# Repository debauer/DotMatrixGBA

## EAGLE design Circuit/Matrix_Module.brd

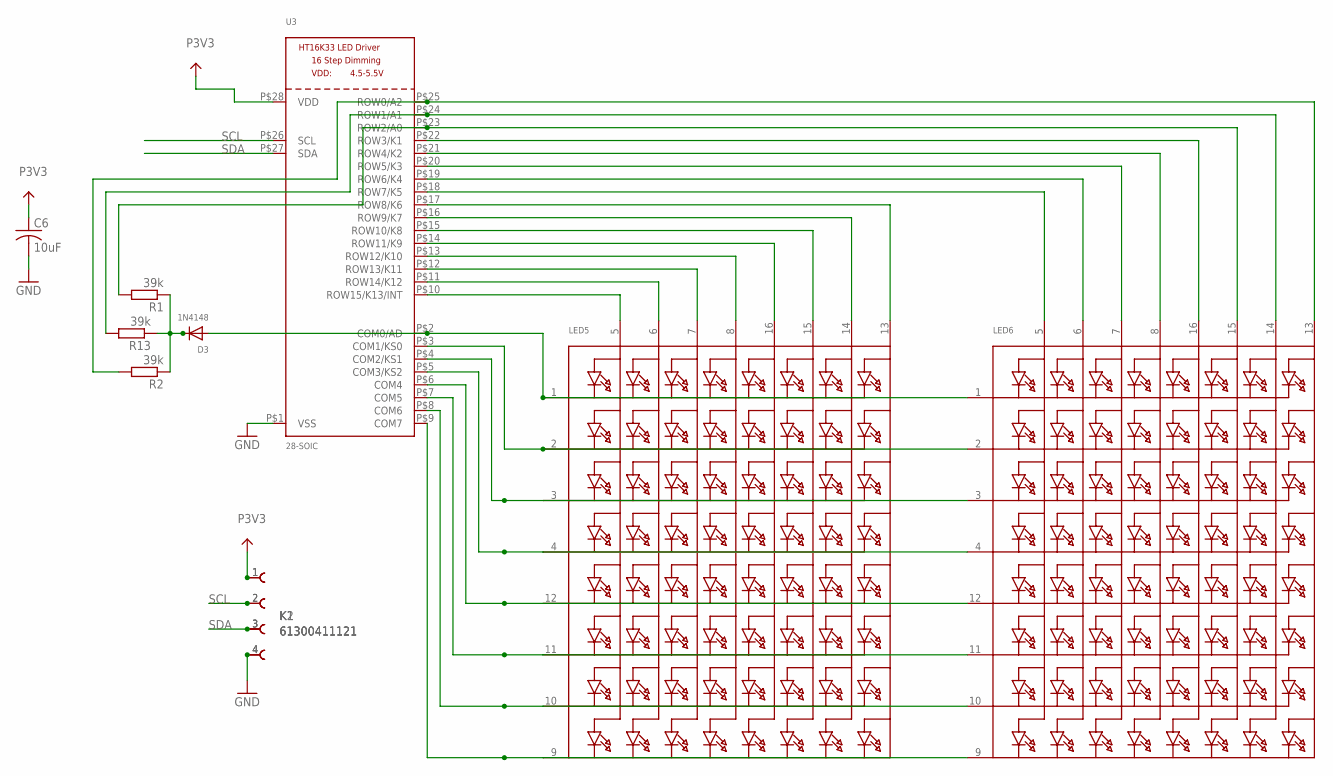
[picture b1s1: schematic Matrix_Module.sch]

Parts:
C6: 10uF; C0805
D3: 1N4148; SOD-323F
K1, K2: 61300411121
LED5, LED6: SEGMENT_8X8_ROWCATHODE; SEGMENT_BL-M07C881UR
R1, R2, R13: 39k; R0805
U3: 28-SOIC; SOP28_300MIL

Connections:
GND: C6.2, K1.4, K2.4, U3.P$1 (VSS)
unnamed: LED6.13 (A8), R2.2, U3.P$25 (ROW0/A2)
unnamed: LED6.14 (A7), R13.2, U3.P$24 (ROW1/A1)
unnamed: LED6.15 (A6), R1.2, U3.P$23 (ROW2/A0)
unnamed: LED5.9 (K8), LED6.9 (K8), U3.P$9 (COM7)
unnamed: LED5.10 (K7), LED6.10 (K7), U3.P$8 (COM6)
unnamed: LED5.11 (K6), LED6.11 (K6), U3.P$7 (COM5)
unnamed: LED5.12 (K5), LED6.12 (K5), U3.P$6 (COM4)
unnamed: LED5.4 (K4), LED6.4 (K4), U3.P$5 (COM3/KS2)
unnamed: LED5.3 (K3), LED6.3 (K3), U3.P$4 (COM2/KS1)
unnamed: LED5.6 (A2), U3.P$11 (ROW14/K12)
unnamed: LED5.7 (A3), U3.P$12 (ROW13/K11)
unnamed: LED6.5 (A1), U3.P$18 (ROW7/K5)
unnamed: LED6.8 (A4), U3.P$21 (ROW4/K2)
unnamed: LED6.7 (A3), U3.P$20 (ROW5/K3)
unnamed: LED5.13 (A8), U3.P$17 (ROW8/K6)
unnamed: LED5.14 (A7), U3.P$16 (ROW9/K7)
unnamed: LED5.16 (A5), U3.P$14 (ROW11/K9)
unnamed: LED5.15 (A6), U3.P$15 (ROW10/K8)
unnamed: LED5.8 (A4), U3.P$13 (ROW12/K10)
unnamed: LED5.5 (A1), U3.P$10 (ROW15/K13/INT)
unnamed: D3.C, R1.1, R2.1, R13.1
unnamed: LED6.16 (A5), U3.P$22 (ROW3/K1)
unnamed: LED6.6 (A2), U3.P$19 (ROW6/K4)
unnamed: D3.A, LED5.1 (K1), LED6.1 (K1), U3.P$2 (COM0/AD)
unnamed: LED5.2 (K2), LED6.2 (K2), U3.P$3 (COM1/KS0)
P3V3: C6.1, K1.1, K2.1, U3.P$28 (VDD)
SCL: K1.2, K2.2, U3.P$26 (SCL)
SDA: K1.3, K2.3, U3.P$27 (SDA)

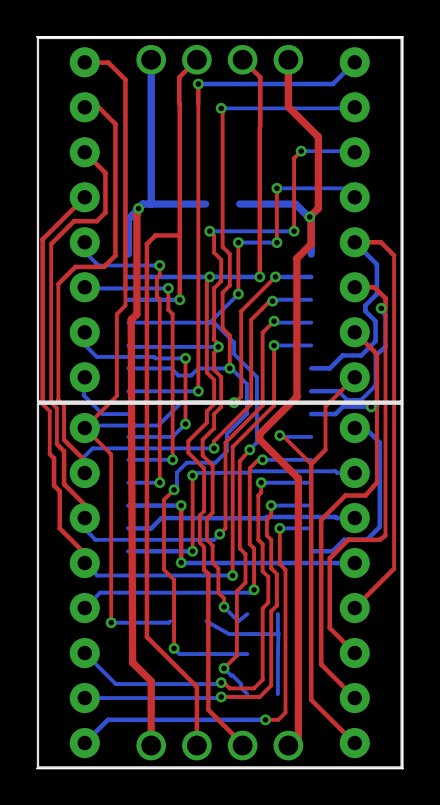
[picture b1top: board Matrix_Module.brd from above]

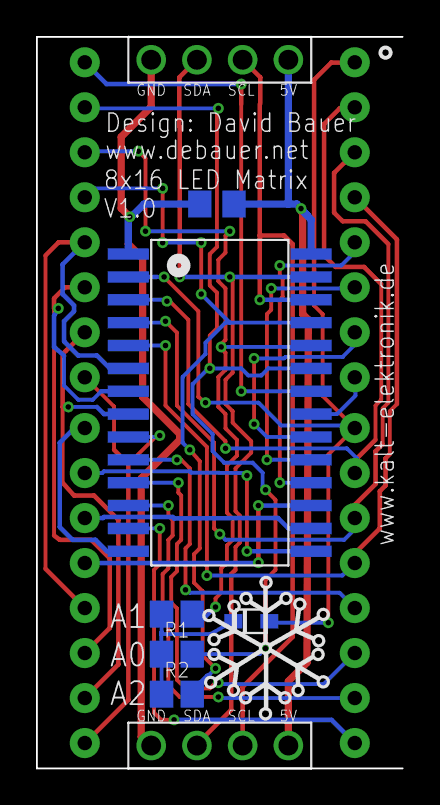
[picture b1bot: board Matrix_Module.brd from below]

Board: 2 copper layers, 20.3 x 40.6 mm, 11 parts (9 on the bottom side), 29 nets.

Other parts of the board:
U$1: SNOW

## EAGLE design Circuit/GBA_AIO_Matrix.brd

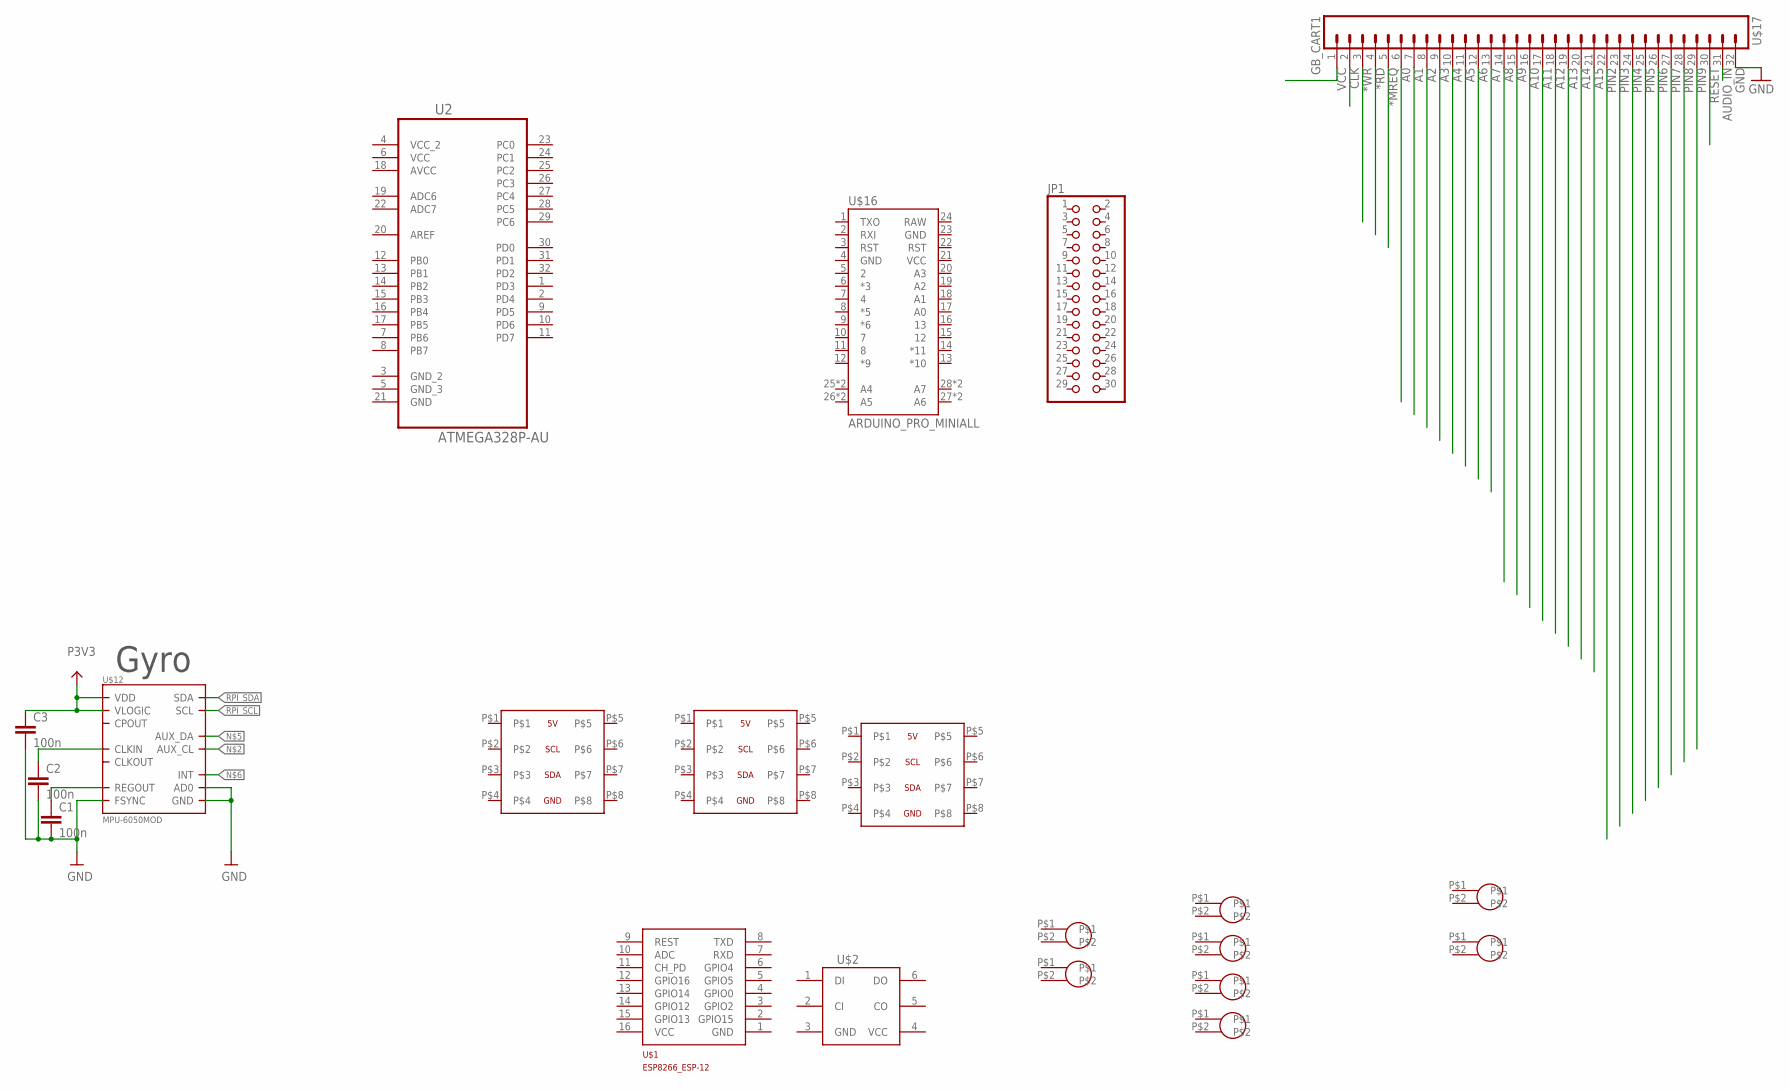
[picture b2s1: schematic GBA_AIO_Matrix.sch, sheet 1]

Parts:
C1, C2, C3: 100n; C0603
JP1: PINHD-2X15/90; 2X15/90
U2: ATMEGA328P-AU; QFP80P900X900X120-32N
U$1: ESP8266_ESP-12; ESP8266-ESP12
U$2: APA102; LED5050
U$4, U$5: GBA_BUTTONAB; GBA_AB
U$6, U$7, U$8, U$9: GBA_BUTTONDIREKTION; GBA_DIREKTION
U$10, U$11: GBA_BUTTONSTART; GBA_START
U$12: MPU-6050MOD; QFN.24.4X4.MOD
U$16: ARDUINO_PRO_MINIALL; ARDUINO_PRO_MINI
U$17: GB_CART1; GB_CART_1
U$18, U$19, U$20: DEBAUER_18X6MATRIX; DEBAUER_16X8MATRIX

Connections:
*MREQ: U$17.5
*RD: U$17.4
*WR: U$17.3
A0: U$17.6; also elsewhere on the board
A1: U$17.7; also elsewhere on the board
A2: U$17.8; also elsewhere on the board
A3: U$17.9
A4: U$17.10
A5: U$17.11
A6: U$17.12
A7: U$17.13
A8: U$17.14
A9: U$17.15
A10: U$17.16
A11: U$17.17
A12: U$17.18
A13: U$17.19
A14: U$17.20
A15: U$17.21
AUDIO_IN: U$17.31
AVCC: U2.18 (AVCC)
GND: C1.2, C2.2, C3.2, U$12.9 (AD0), U$12.11 (FSYNC), U$12.18 (GND), U$17.2, U$17.32; also elsewhere on the board
unnamed: C2.1, U$12.1 (CLKIN)
unnamed: C1.1, U$12.10 (REGOUT)
P3V3: C3.1, U$12.8 (VLOGIC), U$12.13 (VDD); also elsewhere on the board
PIN2: U$17.22
PIN3: U$17.23
PIN4: U$17.24
PIN5: U$17.25
PIN6: U$17.26
PIN7: U$17.27
PIN8: U$17.28
PIN9: U$17.29
RPI_SCL: U$12.23 (SCL)
RPI_SDA: U$12.24 (SDA)
VCC: U2.6 (VCC)
VCC1: U$17.1, U$17.30
VCC_2: U2.4 (VCC_2)

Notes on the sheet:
Gyro
CLK
VCC
RESET

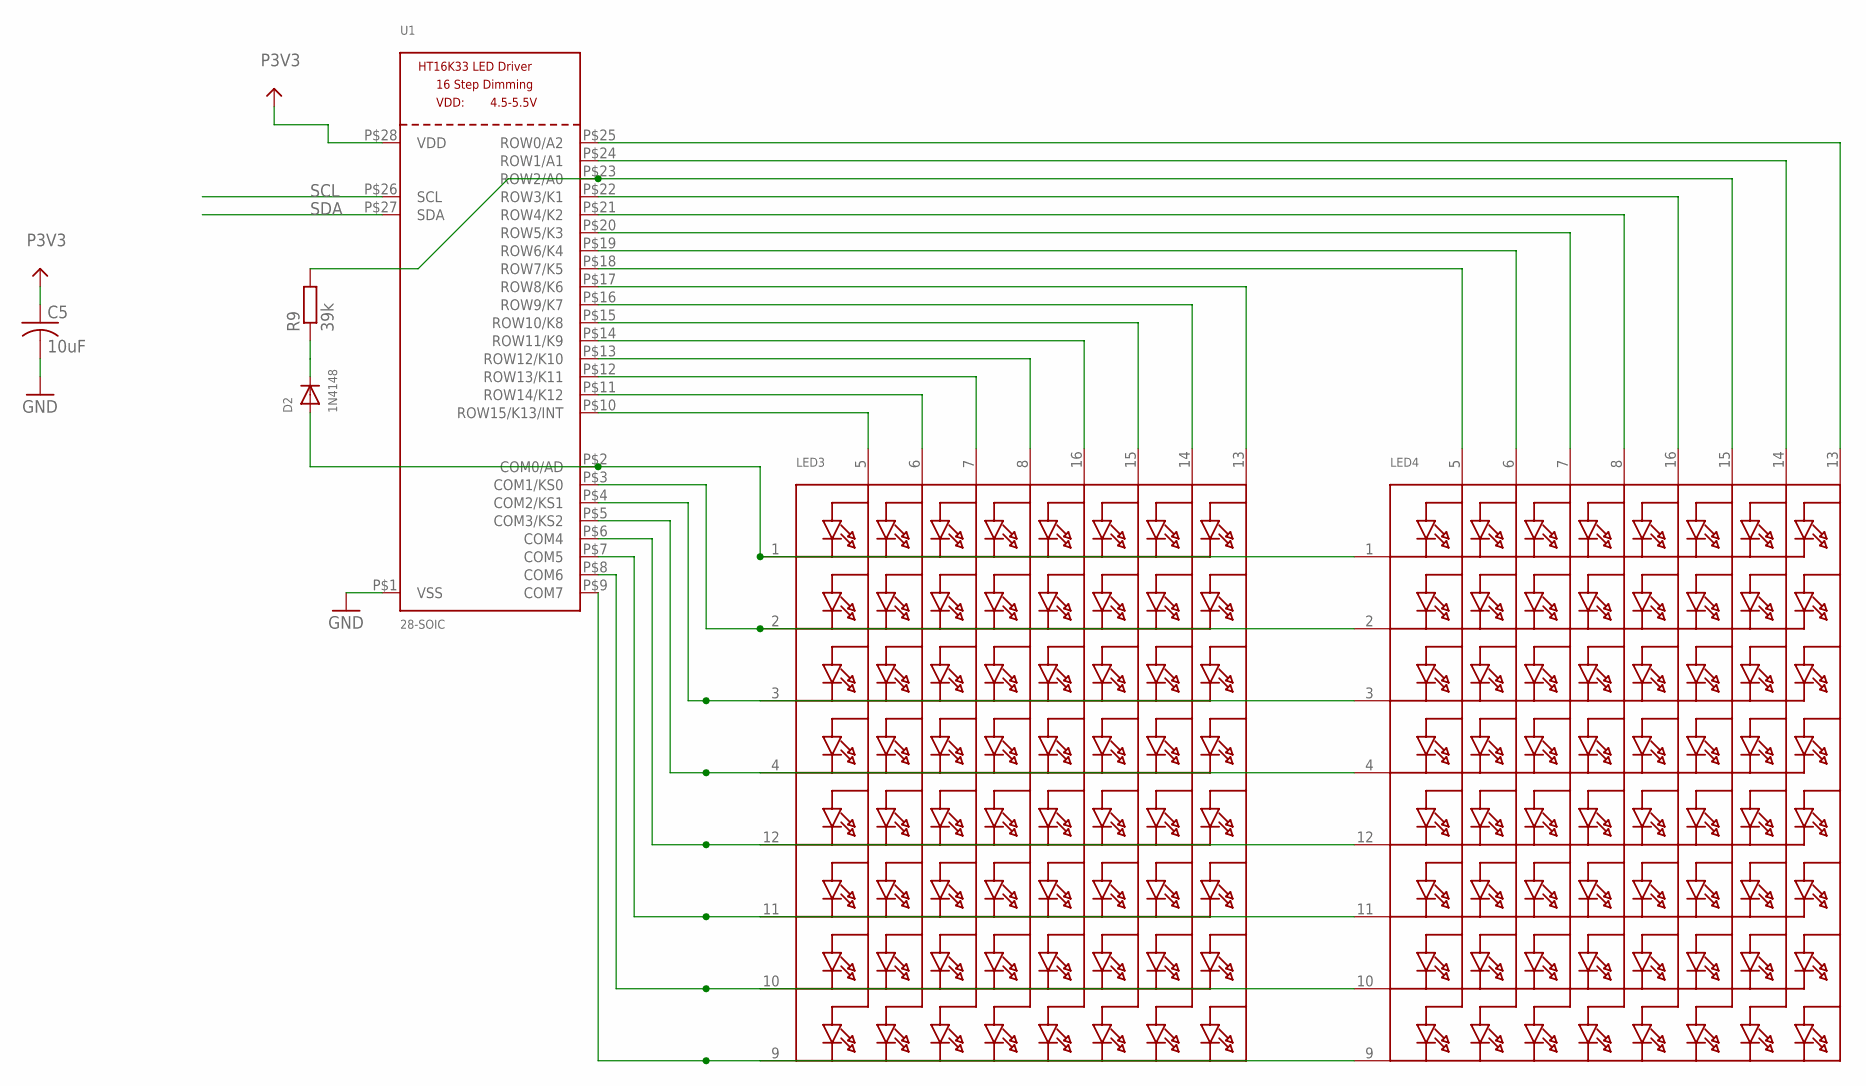
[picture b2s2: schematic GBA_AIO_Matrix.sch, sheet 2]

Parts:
C5: 10uF; C0805
D2: 1N4148; SOD-323F
LED3, LED4: SEGMENT_8X8_ROWCATHODE; SEGMENT_BL-M07C881UR
R9: 39k; R0805
U1: 28-SOIC; SOP28_300MIL

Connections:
GND: C5.2, U1.P$1 (VSS); also elsewhere on the board
unnamed: LED4.13 (A8), U1.P$25 (ROW0/A2)
unnamed: LED4.15 (A6), R9.2, U1.P$23 (ROW2/A0)
unnamed: LED4.14 (A7), U1.P$24 (ROW1/A1)
unnamed: LED3.9 (K8), LED4.9 (K8), U1.P$9 (COM7)
unnamed: LED3.10 (K7), LED4.10 (K7), U1.P$8 (COM6)
unnamed: LED3.11 (K6), LED4.11 (K6), U1.P$7 (COM5)
unnamed: LED3.12 (K5), LED4.12 (K5), U1.P$6 (COM4)
unnamed: LED3.4 (K4), LED4.4 (K4), U1.P$5 (COM3/KS2)
unnamed: LED3.3 (K3), LED4.3 (K3), U1.P$4 (COM2/KS1)
unnamed: LED3.6 (A2), U1.P$11 (ROW14/K12)
unnamed: LED3.7 (A3), U1.P$12 (ROW13/K11)
unnamed: LED4.5 (A1), U1.P$18 (ROW7/K5)
unnamed: LED4.8 (A4), U1.P$21 (ROW4/K2)
unnamed: LED4.7 (A3), U1.P$20 (ROW5/K3)
unnamed: LED3.13 (A8), U1.P$17 (ROW8/K6)
unnamed: LED3.14 (A7), U1.P$16 (ROW9/K7)
unnamed: LED3.16 (A5), U1.P$14 (ROW11/K9)
unnamed: LED3.15 (A6), U1.P$15 (ROW10/K8)
unnamed: LED3.8 (A4), U1.P$13 (ROW12/K10)
unnamed: LED3.5 (A1), U1.P$10 (ROW15/K13/INT)
unnamed: D2.C, R9.1
unnamed: LED4.16 (A5), U1.P$22 (ROW3/K1)
unnamed: LED4.6 (A2), U1.P$19 (ROW6/K4)
unnamed: D2.A, LED3.1 (K1), LED4.1 (K1), U1.P$2 (COM0/AD)
unnamed: LED3.2 (K2), LED4.2 (K2), U1.P$3 (COM1/KS0)
P3V3: C5.1, U1.P$28 (VDD); also elsewhere on the board
SCL: U1.P$26 (SCL); also elsewhere on the board
SDA: U1.P$27 (SDA); also elsewhere on the board

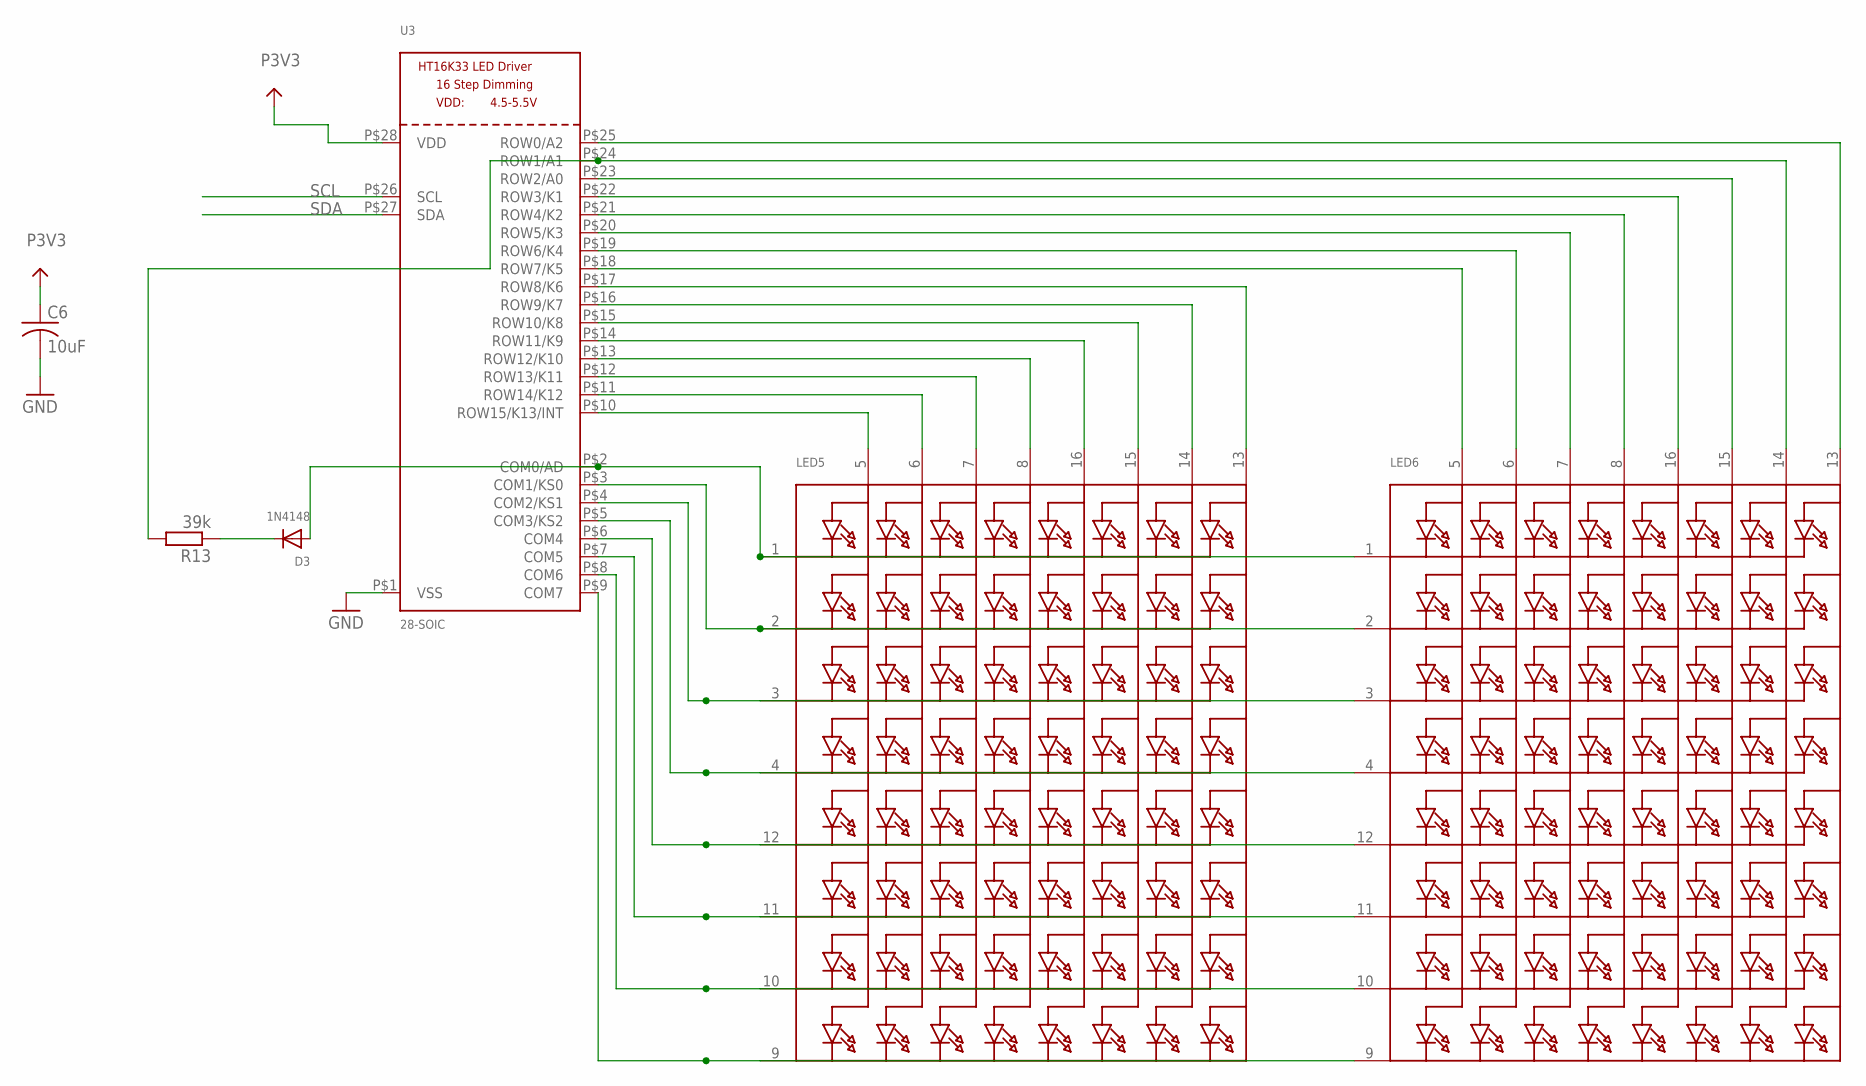
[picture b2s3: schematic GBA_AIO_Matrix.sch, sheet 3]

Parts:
C6: 10uF; C0805
D3: 1N4148; SOD-323F
LED5, LED6: SEGMENT_8X8_ROWCATHODE; SEGMENT_BL-M07C881UR
R13: 39k; R0805
U3: 28-SOIC; SOP28_300MIL

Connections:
GND: C6.2, U3.P$1 (VSS); also elsewhere on the board
unnamed: LED6.13 (A8), U3.P$25 (ROW0/A2)
unnamed: LED6.14 (A7), R13.2, U3.P$24 (ROW1/A1)
unnamed: LED6.15 (A6), U3.P$23 (ROW2/A0)
unnamed: LED5.9 (K8), LED6.9 (K8), U3.P$9 (COM7)
unnamed: LED5.10 (K7), LED6.10 (K7), U3.P$8 (COM6)
unnamed: LED5.11 (K6), LED6.11 (K6), U3.P$7 (COM5)
unnamed: LED5.12 (K5), LED6.12 (K5), U3.P$6 (COM4)
unnamed: LED5.4 (K4), LED6.4 (K4), U3.P$5 (COM3/KS2)
unnamed: LED5.3 (K3), LED6.3 (K3), U3.P$4 (COM2/KS1)
unnamed: LED5.6 (A2), U3.P$11 (ROW14/K12)
unnamed: LED5.7 (A3), U3.P$12 (ROW13/K11)
unnamed: LED6.5 (A1), U3.P$18 (ROW7/K5)
unnamed: LED6.8 (A4), U3.P$21 (ROW4/K2)
unnamed: LED6.7 (A3), U3.P$20 (ROW5/K3)
unnamed: LED5.13 (A8), U3.P$17 (ROW8/K6)
unnamed: LED5.14 (A7), U3.P$16 (ROW9/K7)
unnamed: LED5.16 (A5), U3.P$14 (ROW11/K9)
unnamed: LED5.15 (A6), U3.P$15 (ROW10/K8)
unnamed: LED5.8 (A4), U3.P$13 (ROW12/K10)
unnamed: LED5.5 (A1), U3.P$10 (ROW15/K13/INT)
unnamed: D3.C, R13.1
unnamed: LED6.16 (A5), U3.P$22 (ROW3/K1)
unnamed: LED6.6 (A2), U3.P$19 (ROW6/K4)
unnamed: D3.A, LED5.1 (K1), LED6.1 (K1), U3.P$2 (COM0/AD)
unnamed: LED5.2 (K2), LED6.2 (K2), U3.P$3 (COM1/KS0)
P3V3: C6.1, U3.P$28 (VDD); also elsewhere on the board
SCL: U3.P$26 (SCL); also elsewhere on the board
SDA: U3.P$27 (SDA); also elsewhere on the board

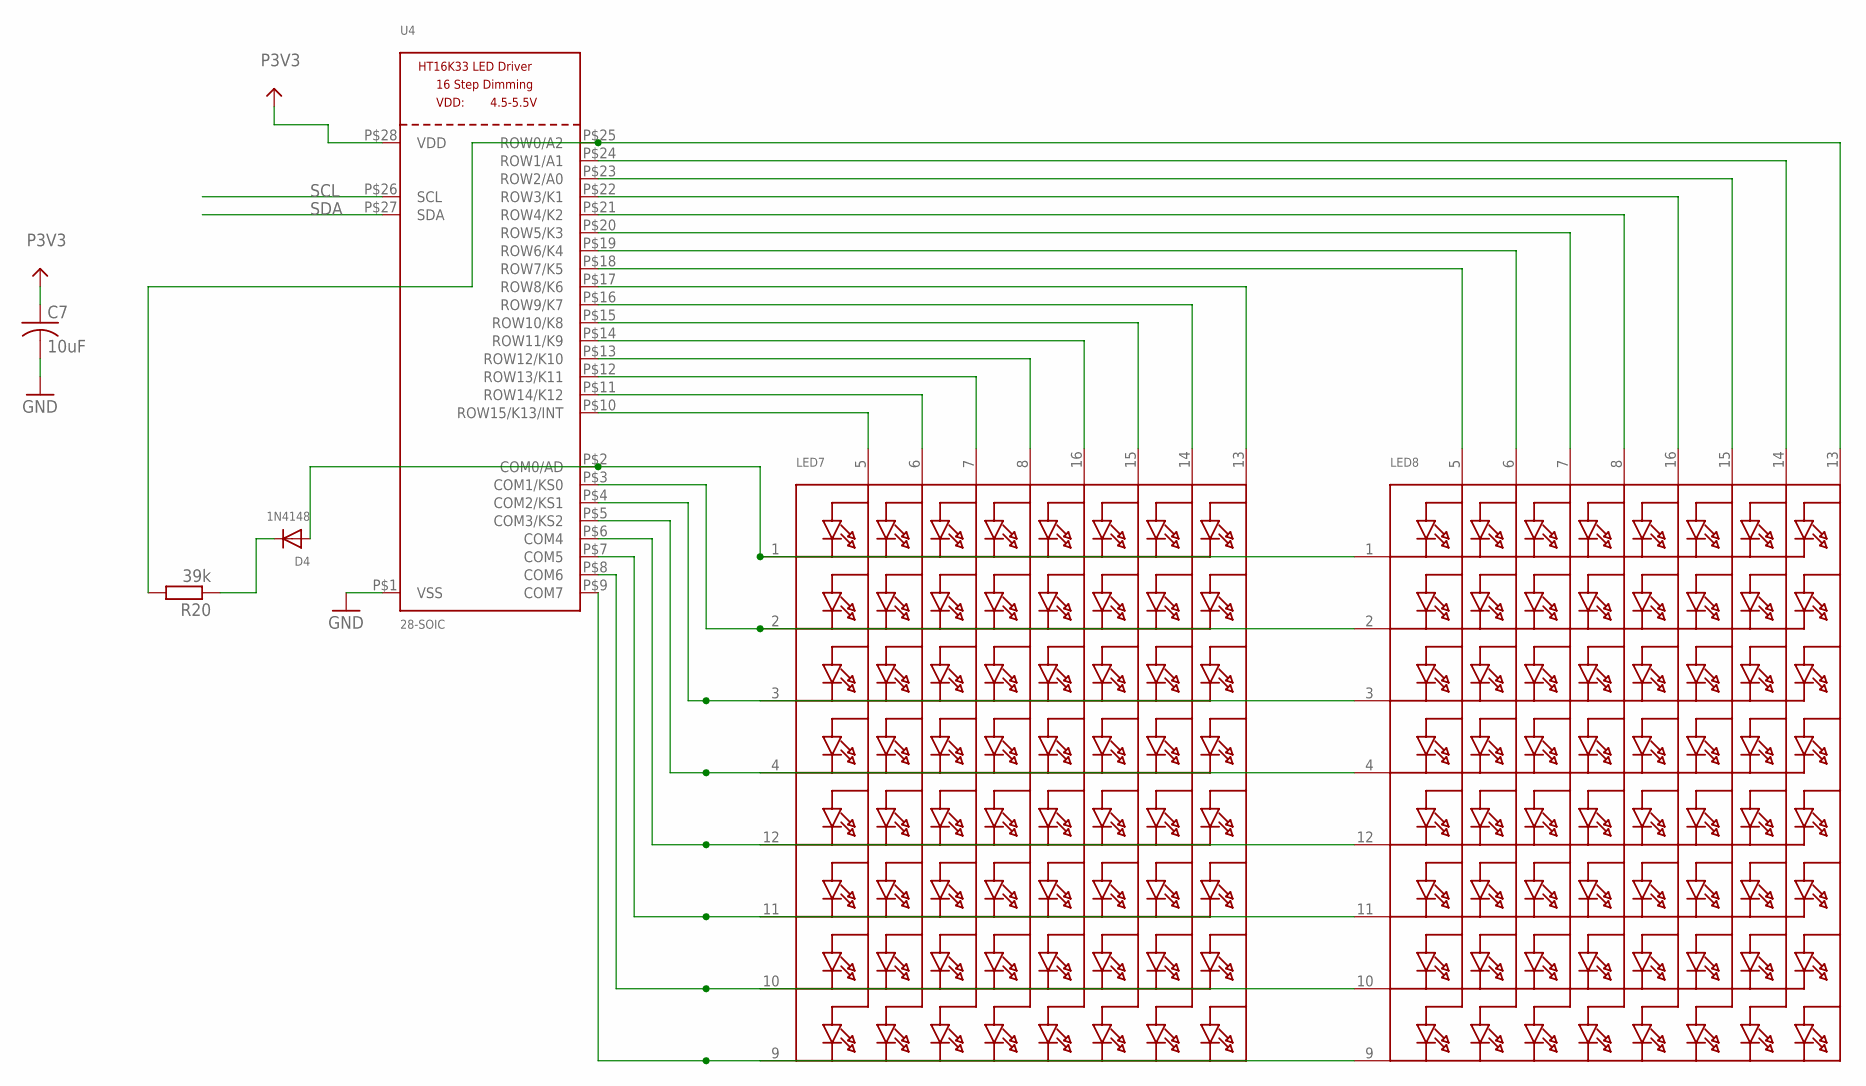
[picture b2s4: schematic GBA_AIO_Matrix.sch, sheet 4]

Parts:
C7: 10uF; C0805
D4: 1N4148; SOD-323F
LED7, LED8: SEGMENT_8X8_ROWCATHODE; SEGMENT_BL-M07C881UR
R20: 39k; R0805
U4: 28-SOIC; SOP28_300MIL

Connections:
A0: LED8.15 (A6), U4.P$23 (ROW2/A0); also elsewhere on the board
A1: LED8.14 (A7), U4.P$24 (ROW1/A1); also elsewhere on the board
A2: LED8.13 (A8), R20.2, U4.P$25 (ROW0/A2); also elsewhere on the board
GND: C7.2, U4.P$1 (VSS); also elsewhere on the board
unnamed: LED7.9 (K8), LED8.9 (K8), U4.P$9 (COM7)
unnamed: LED7.10 (K7), LED8.10 (K7), U4.P$8 (COM6)
unnamed: LED7.11 (K6), LED8.11 (K6), U4.P$7 (COM5)
unnamed: LED7.12 (K5), LED8.12 (K5), U4.P$6 (COM4)
unnamed: LED7.4 (K4), LED8.4 (K4), U4.P$5 (COM3/KS2)
unnamed: LED7.3 (K3), LED8.3 (K3), U4.P$4 (COM2/KS1)
unnamed: LED7.6 (A2), U4.P$11 (ROW14/K12)
unnamed: LED7.7 (A3), U4.P$12 (ROW13/K11)
unnamed: LED8.5 (A1), U4.P$18 (ROW7/K5)
unnamed: LED8.8 (A4), U4.P$21 (ROW4/K2)
unnamed: LED8.7 (A3), U4.P$20 (ROW5/K3)
unnamed: LED7.13 (A8), U4.P$17 (ROW8/K6)
unnamed: LED7.14 (A7), U4.P$16 (ROW9/K7)
unnamed: LED7.16 (A5), U4.P$14 (ROW11/K9)
unnamed: LED7.15 (A6), U4.P$15 (ROW10/K8)
unnamed: LED7.8 (A4), U4.P$13 (ROW12/K10)
unnamed: LED7.5 (A1), U4.P$10 (ROW15/K13/INT)
unnamed: D4.C, R20.1
unnamed: LED8.16 (A5), U4.P$22 (ROW3/K1)
unnamed: LED8.6 (A2), U4.P$19 (ROW6/K4)
unnamed: D4.A, LED7.1 (K1), LED8.1 (K1), U4.P$2 (COM0/AD)
unnamed: LED7.2 (K2), LED8.2 (K2), U4.P$3 (COM1/KS0)
P3V3: C7.1, U4.P$28 (VDD); also elsewhere on the board
SCL: U4.P$26 (SCL); also elsewhere on the board
SDA: U4.P$27 (SDA); also elsewhere on the board

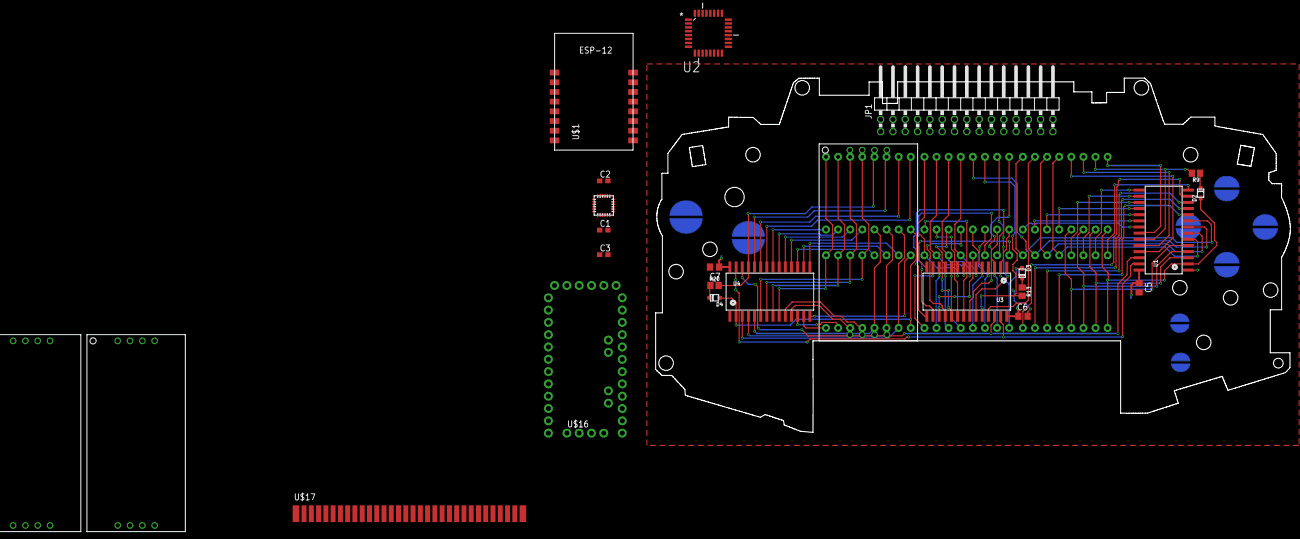
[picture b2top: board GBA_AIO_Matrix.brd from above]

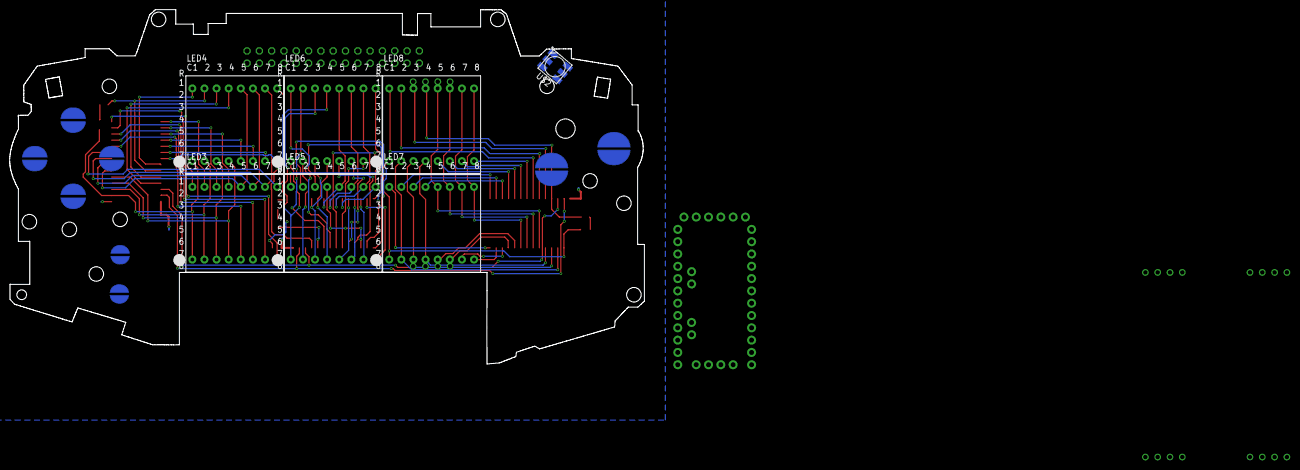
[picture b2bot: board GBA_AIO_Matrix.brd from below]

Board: 2 copper layers, 131.0 x 73.1 mm, 39 parts (15 on the bottom side), 82 nets.

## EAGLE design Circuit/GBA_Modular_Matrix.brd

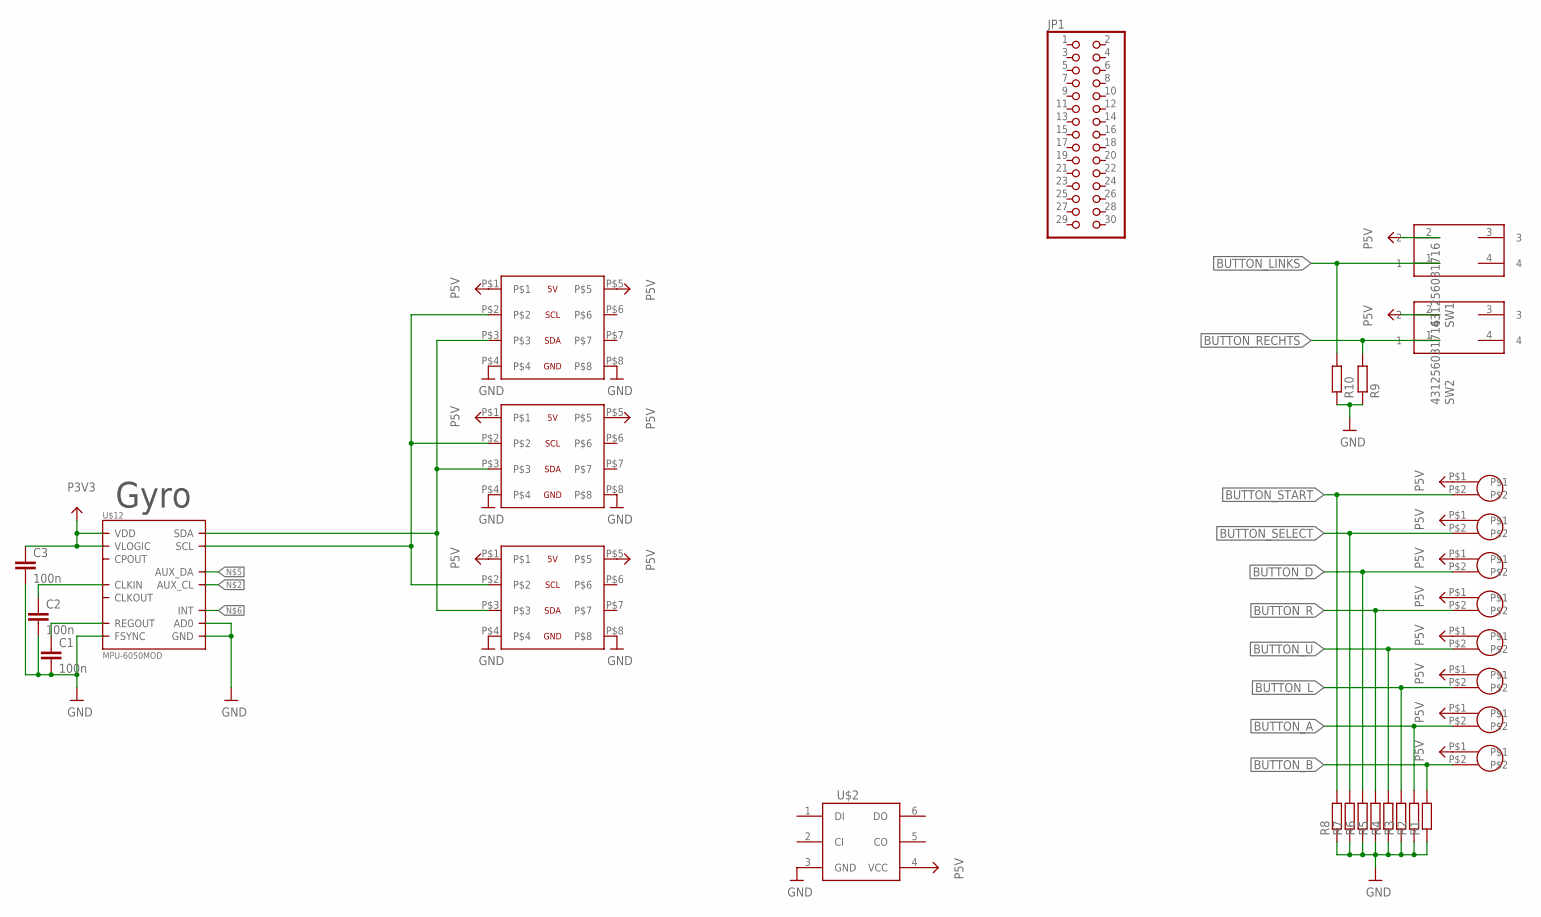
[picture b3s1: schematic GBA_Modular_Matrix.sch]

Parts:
C1, C2, C3: 100n; C0603
JP1: PINHD-2X15; 2X15
R1, R2, R3, R4, R5, R6, R7, R8, R9, R10: R-EU_R0805; R0805
SW1, SW2: 431256031716
U$2: APA102; LED5050
U$4, U$5: GBA_BUTTONAB; GBA_AB
U$6, U$7, U$8, U$9: GBA_BUTTONDIREKTION; GBA_DIREKTION
U$10, U$11: GBA_BUTTONSTART; GBA_START
U$12: MPU-6050MOD; QFN.24.4X4.MOD
U$18, U$19, U$20: DEBAUER_18X6MATRIX; DEBAUER_16X8MATRIX

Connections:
BUTTON_A: R2.2, U$4.P$2
BUTTON_B: R1.2, U$5.P$2
BUTTON_D: R6.2, U$6.P$2
BUTTON_L: R3.2, U$9.P$2
BUTTON_LINKS: R10.2, SW1.1
BUTTON_R: R5.2, U$7.P$2
BUTTON_RECHTS: R9.2, SW2.1
BUTTON_SELECT: R7.2, U$11.P$2
BUTTON_START: R8.2, U$10.P$2
BUTTON_U: R4.2, U$8.P$2
GND: C1.2, C2.2, C3.2, R1.1, R2.1, R3.1, R4.1, R5.1, R6.1, R7.1, R8.1, R9.1, R10.1, U$2.3 (GND), U$12.9 (AD0), U$12.11 (FSYNC), U$12.18 (GND), U$18.P$4, U$18.P$8, U$19.P$4, U$19.P$8, U$20.P$4, U$20.P$8
unnamed: C2.1, U$12.1 (CLKIN)
unnamed: C1.1, U$12.10 (REGOUT)
unnamed: U$12.23 (SCL), U$18.P$2, U$19.P$2, U$20.P$2
unnamed: U$12.24 (SDA), U$18.P$3, U$19.P$3, U$20.P$3
P3V3: C3.1, U$12.8 (VLOGIC), U$12.13 (VDD)
P5V: SW1.2, SW2.2, U$2.4 (VCC), U$4.P$1, U$5.P$1, U$6.P$1, U$7.P$1, U$8.P$1, U$9.P$1, U$10.P$1, U$11.P$1, U$18.P$1, U$18.P$5, U$19.P$1, U$19.P$5, U$20.P$1, U$20.P$5

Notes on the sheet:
Gyro

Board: 2 copper layers, 29 parts (11 on the bottom side), 17 nets, no tracks yet.

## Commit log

2019-01-29 initial commit with old files

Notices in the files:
parts and their libraries:
Wuerth_Elektronik_Switch: Copyright: Würth Elektronik
